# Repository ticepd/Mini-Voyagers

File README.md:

# Mini-Voyager-1 & Mini-Voyager-2 schematic and board files

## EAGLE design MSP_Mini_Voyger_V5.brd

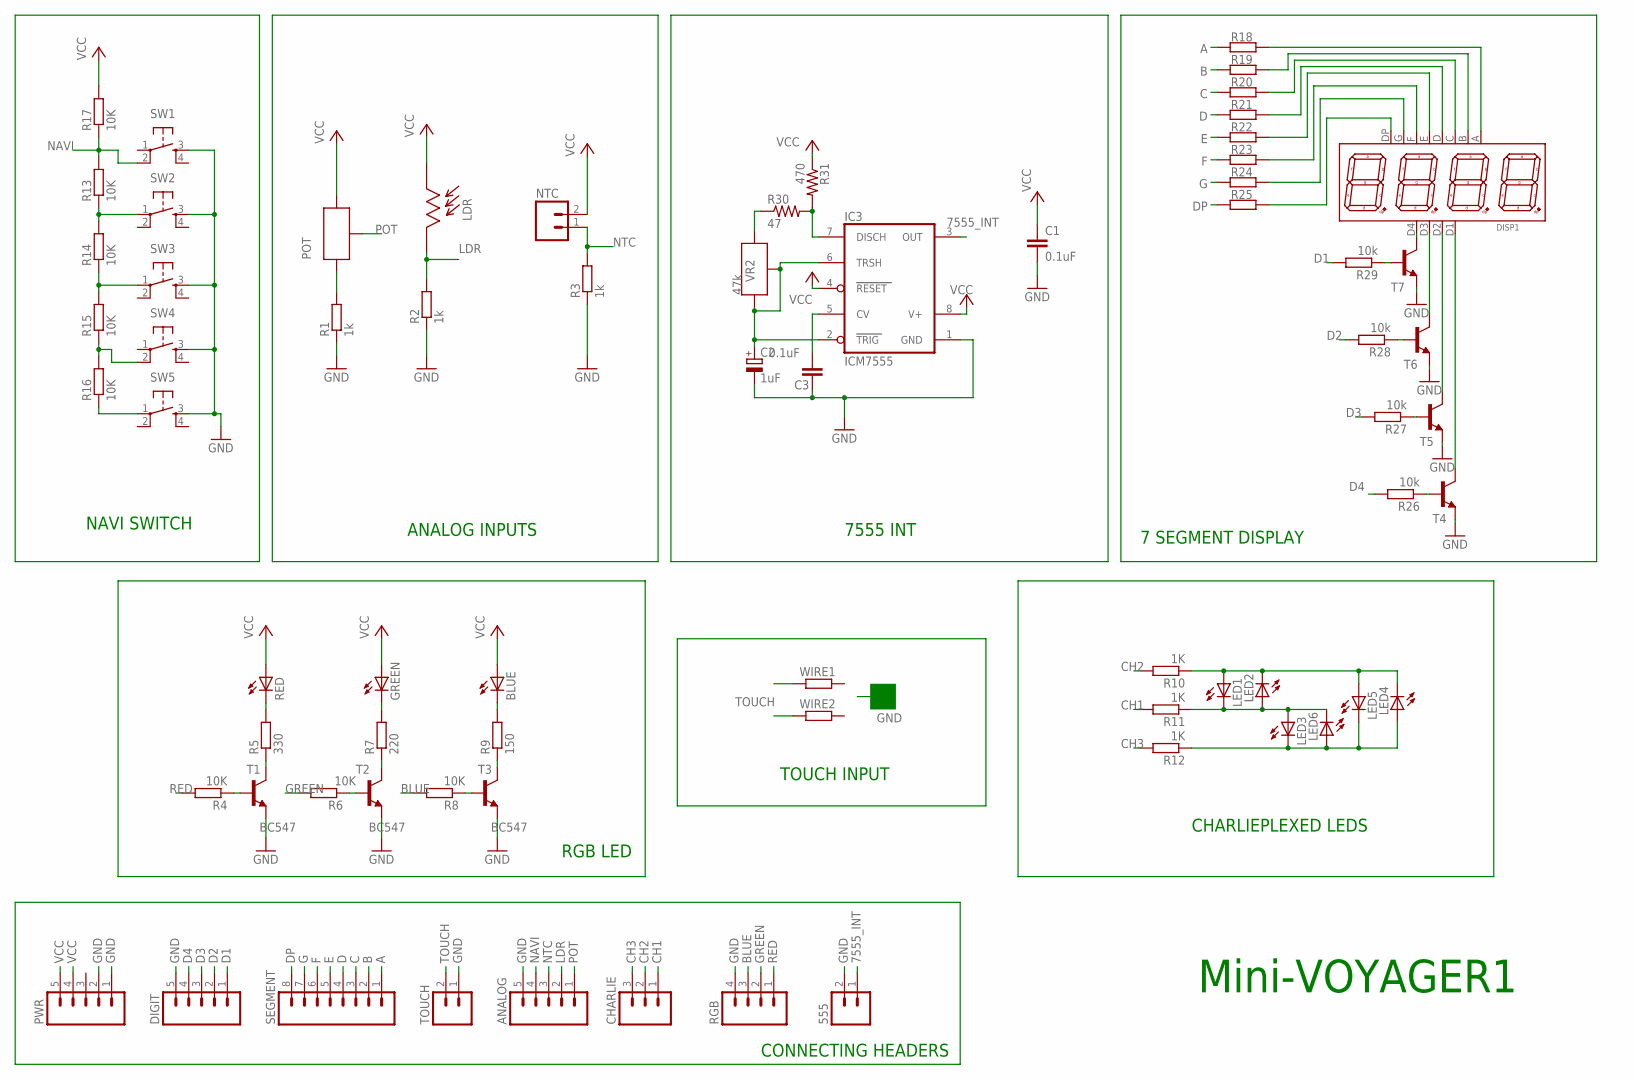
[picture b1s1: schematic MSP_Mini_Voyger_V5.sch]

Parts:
555: M02; 02P
ANALOG: M05; 05P
BLUE: LED5MM
C1: 0.1uF; C050-024X044
C2: 1uF; E2,5-7
C3: 0.1uF; C025-024X044
CHARLIE: M03; 03P
DIGIT: M05; 05P
DISP1: 7-SEG_4D_0.36; 7SEG-4DIG
GREEN: LED5MM
IC3: ICM7555; DIL08
LDR: CDSLDR3MM; LDR3MM
LED1, LED2, LED3, LED4, LED5, LED6: LED3MM
NTC: M02; 02P
POT: POTNORMAL; RJ9W
PWR: M05; 05P
R1, R2, R3: 1k; 0207/10
R4, R6, R8: 10K; 0207/7
R5: 330; 0207/7
R7: 220; 0207/7
R9: 150; 0207/7
R10, R11, R12: 1K; 0207/10
R13, R14, R15, R16, R17: 10K; 0207/10
R18, R19, R20, R21, R22, R23, R24, R25: 1k; 0207/7
R26, R27, R28, R29: 10k; 0207/7
R30: 47; 0207/7
R31: 470; 0207/7
RED: LED5MM
RGB: M04; 04P
SEGMENT: M08; 08P
SW1, SW2, SW3, SW4, SW5: OMRON_SWITCH_10-XX; B3F-10XX
T1, T2, T3, T4, T5, T6, T7: BC547; TO92
TOUCH: M02; 02P
VR2: 47k; RJ9W
WIRE1, WIRE2: R-EU_0207/15; 0207/15

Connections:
7555_INT: 555.1, IC3.3 (OUT)
A: R18.2, SEGMENT.1
B: R19.2, SEGMENT.2
BLUE: R8.2, RGB.3
C: R20.2, SEGMENT.3
CH1: CHARLIE.1, R11.2
CH2: CHARLIE.2, R10.2
CH3: CHARLIE.3, R12.2
D: R21.2, SEGMENT.4
D1: DIGIT.1, R29.2
D2: DIGIT.2, R28.2
D3: DIGIT.3, R27.2
D4: DIGIT.4, R26.2
DP: R25.2, SEGMENT.8
E: R22.2, SEGMENT.5
F: R23.2, SEGMENT.6
G: R24.2, SEGMENT.7
GND: 555.2, ANALOG.5, C1.2, C2.-, C3.2, DIGIT.5, IC3.1 (GND), PWR.1, PWR.2, R1.1, R2.1, R3.1, RGB.4, SW1.3 (S), SW2.3 (S), SW3.3 (S), SW4.3 (S), SW5.3 (S), T1.1 (E), T2.1 (E), T3.1 (E), T4.1 (E), T5.1 (E), T6.1 (E), T7.1 (E), TOUCH.1
GREEN: R6.2, RGB.2
LDR: ANALOG.2, LDR.P$2, R2.2
unnamed: POT.E, R1.2
unnamed: LED1.A, LED2.K (C), LED4.K (C), LED5.A, R10.1
unnamed: IC3.7 (DISCH), R30.2, R31.2
unnamed: R5.1, T1.3 (C)
unnamed: DISP1.D1, T4.3 (C)
unnamed: DISP1.D4, T7.3 (C)
unnamed: DISP1.A, R18.1
unnamed: DISP1.B, R19.1
unnamed: R4.1, T1.2 (B)
unnamed: R13.1, R14.2, SW2.1
unnamed: R14.1, R15.2, SW3.1
unnamed: R15.1, R16.2, SW4.2 (P1)
unnamed: R16.1, SW5.1
unnamed: R6.1, T2.2 (B)
unnamed: DISP1.C, R20.1
unnamed: DISP1.D, R21.1
unnamed: R5.2, RED.K (C)
unnamed: GREEN.K (C), R7.2
unnamed: DISP1.E, R22.1
unnamed: R8.1, T3.2 (B)
unnamed: R9.1, T3.3 (C)
unnamed: BLUE.K (C), R9.2
unnamed: R26.1, T4.2 (B)
unnamed: R27.1, T5.2 (B)
unnamed: R28.1, T6.2 (B)
unnamed: R29.1, T7.2 (B)
unnamed: DISP1.D2, T5.3 (C)
unnamed: DISP1.D3, T6.3 (C)
unnamed: DISP1.F, R23.1
unnamed: DISP1.G, R24.1
unnamed: DISP1.DP, R25.1
unnamed: C2.+, IC3.2 (TRIG), IC3.6 (TRSH), VR2.E, VR2.S
unnamed: R30.1, VR2.A
unnamed: C3.1, IC3.5 (CV)
unnamed: LED3.K (C), LED4.A, LED5.K (C), LED6.A, R12.1
unnamed: LED1.K (C), LED2.A, LED3.A, LED6.K (C), R11.1
NAVI: ANALOG.4, R13.2, R17.1, SW1.2 (P1)
NTC: ANALOG.3, NTC.1, R3.2
POT: ANALOG.1, POT.S
R7: R7.1, T2.3 (C)
RED: R4.2, RGB.1
TOUCH: TOUCH.2, WIRE1.1, WIRE2.1
VCC: BLUE.A, C1.1, GREEN.A, IC3.4 (RESET), IC3.8 (V+), LDR.P$1, NTC.2, POT.A, PWR.4, PWR.5, R17.2, R31.1, RED.A

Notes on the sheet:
NAVI SWITCH
ANALOG INPUTS
RGB LED
7 SEGMENT DISPLAY
TOUCH INPUT
CHARLIEPLEXED LEDS
7555 INT
CONNECTING HEADERS
Mini-VOYAGER1

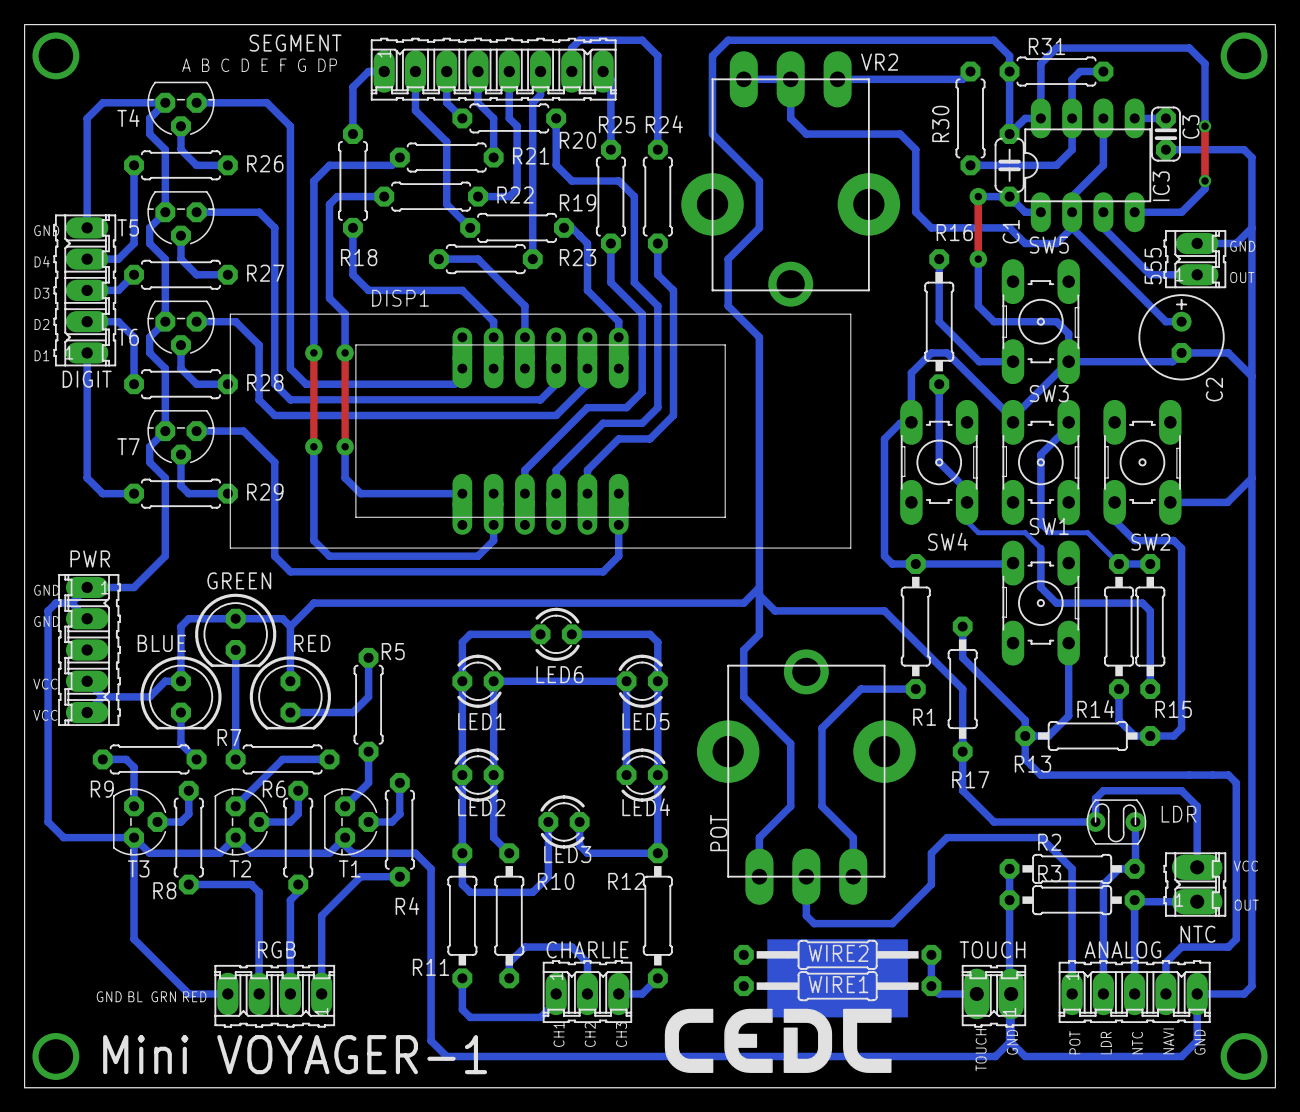
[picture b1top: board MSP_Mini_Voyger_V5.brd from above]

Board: 2 copper layers, 101.6 x 86.4 mm, 72 parts (0 on the bottom side), 63 nets.

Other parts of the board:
U$1: LOGO-CEDT-SILK-18MM

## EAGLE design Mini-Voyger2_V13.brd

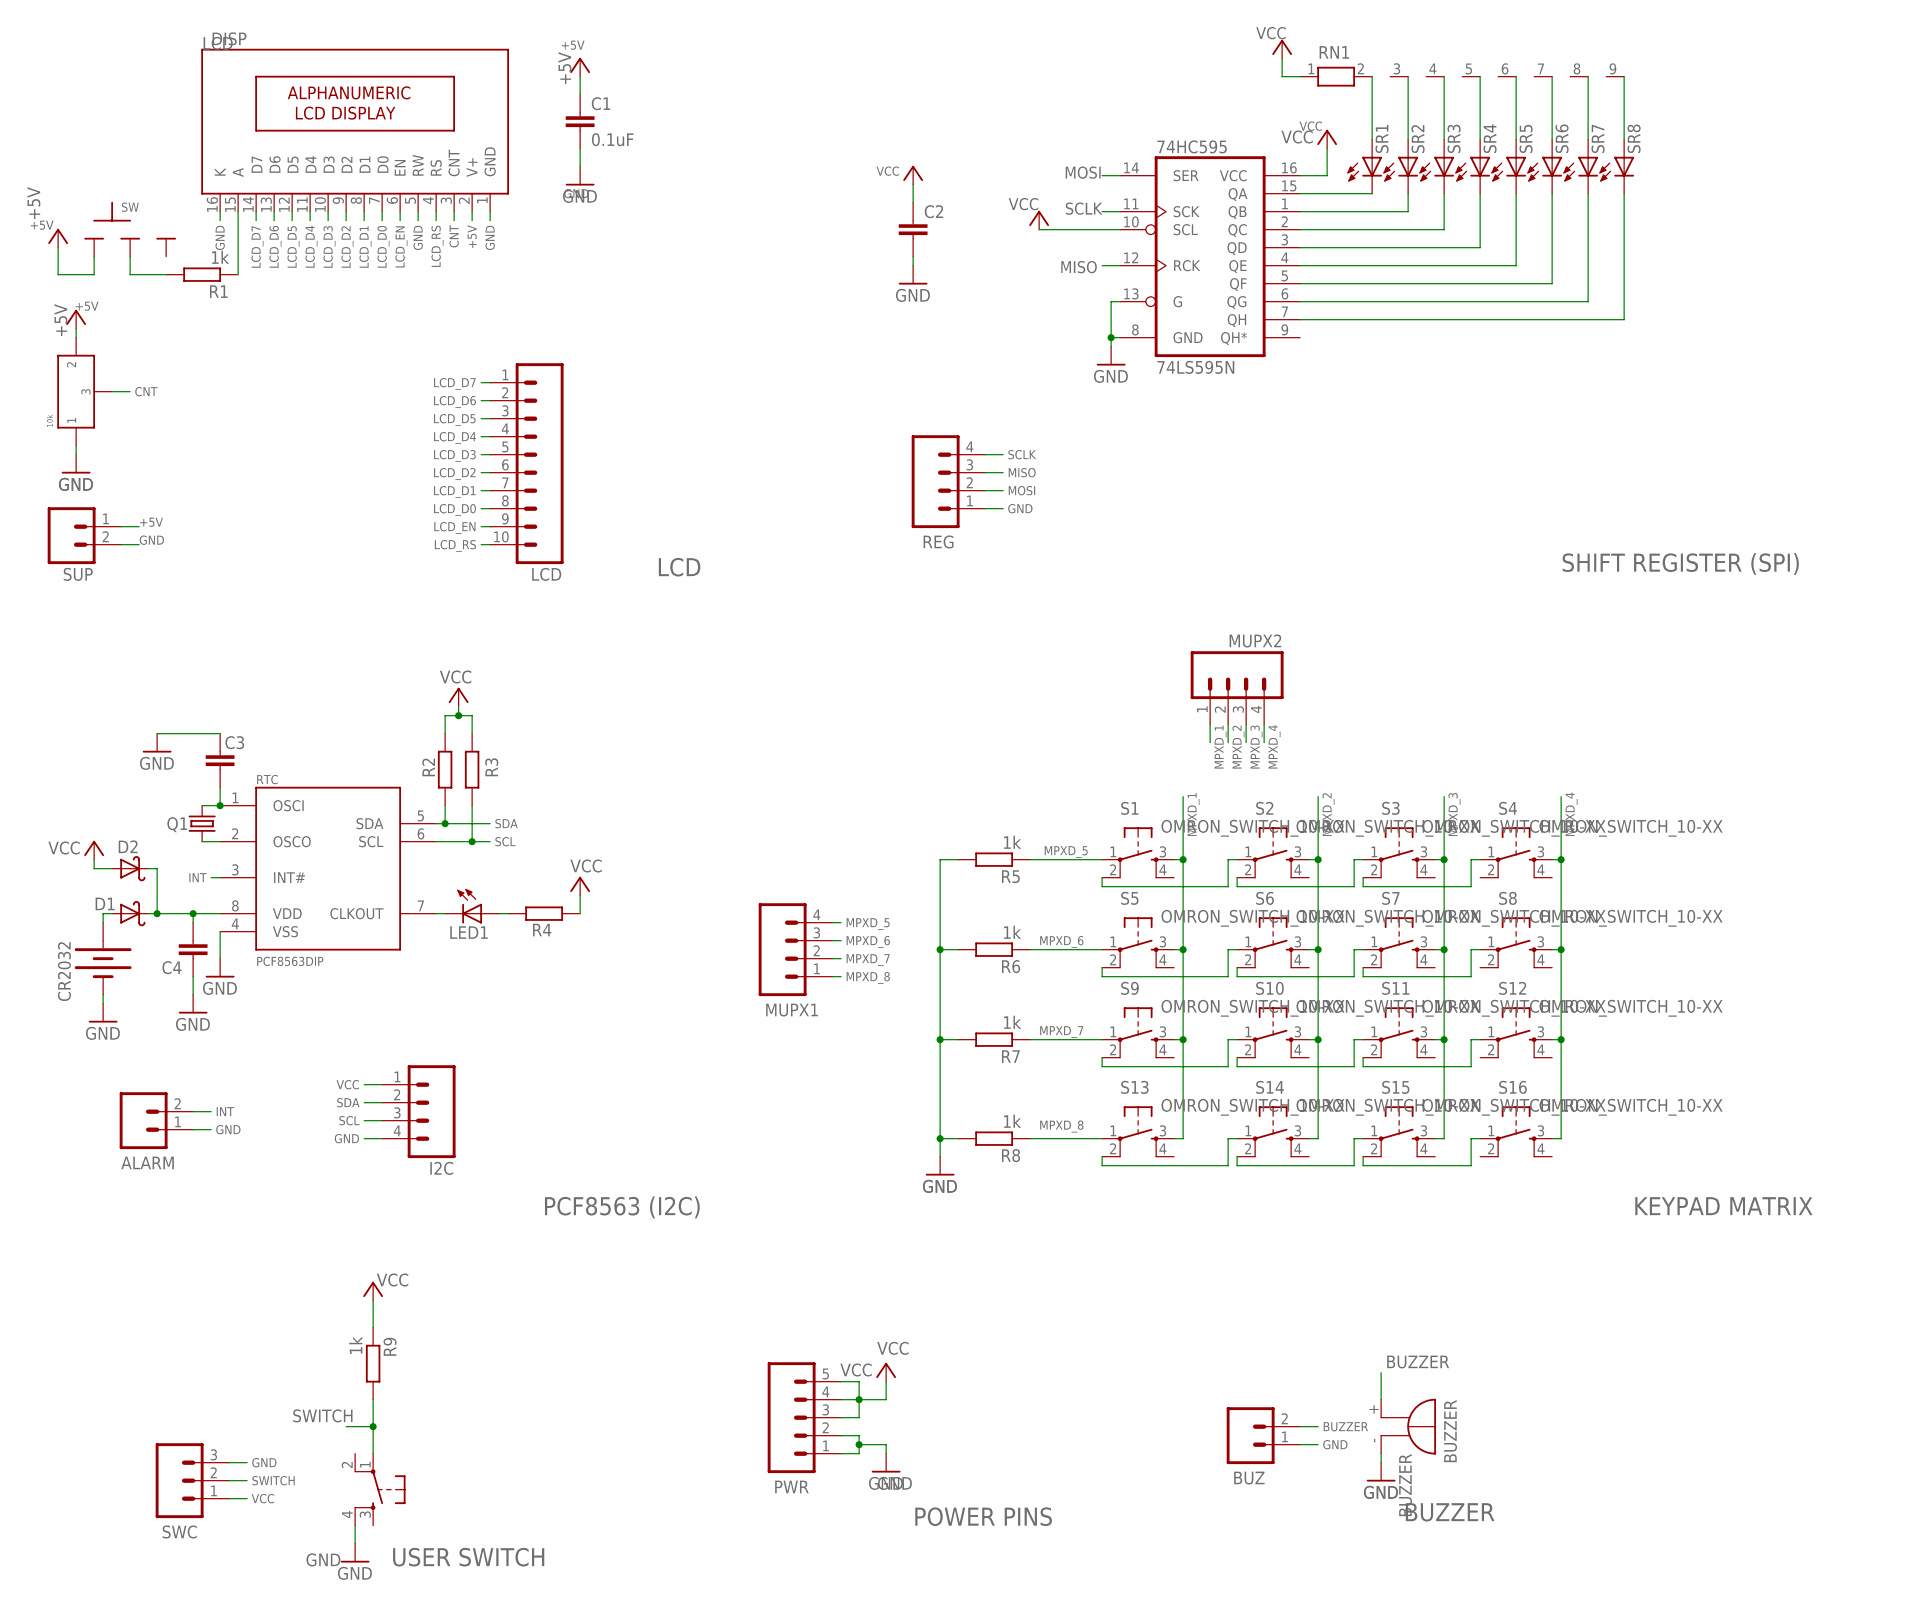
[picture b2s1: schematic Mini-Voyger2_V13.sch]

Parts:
74HC595: 74LS595N; DIL16
ALARM: M02; 02P
BUZ: M02; 02P
BUZZER: BUZZER; F/TMB
C1: 0.1uF; C025-024X044
C2: 0.1uF; C025-025X050
C3: 22pF; C025-024X044
C4: 0.1uF; C050-025X075
CR2032: BATTERY20PTH; BATTCOM_20MM_PTH
D1, D2: 1N5819; DO41-10
DISP: LCD; 16X2_LCD
I2C: M04; 04P
LCD: M10; 10P
LED1: LED3MM
MUPX1, MUPX2: M04; 04P
PRESET: 10k; PRESET_LR
PWR: M05; 05P
Q1: 32678Hz; TC26H
R1, R5, R6, R7, R8, R9: 1k; 0207/7
R2, R3: 10k; 0207/7
R4: 470; 0207/7
REG: M04; 04P
RN1: 1k; RN-9
RTC: PCF8563DIP; DIL08
S1, S2, S3, S4, S5, S6, S7, S8, S9, S10, S11, S12, S13, S14, S15, S16: OMRON_SWITCH_10-XX; B3F-10XX
SR1, SR2, SR3, SR4, SR5, SR6, SR7, SR8: LED3MM
SUP: M02; 02P
SW: SLIDESWITCH-BIG; BIGSWITCH
SW1: OMRON_SWITCH_10-XX; B3F-10XX
SWC: M03; 03P

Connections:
+5V: C1.1, DISP.2 (V+), PRESET.P$2 (2), SUP.1, SW.1
BUZZER: BUZ.2, BUZZER.+
CNT: DISP.3 (CNT), PRESET.P$3 (3)
GND: 74HC595.8 (GND), 74HC595.13 (G), ALARM.1, BUZ.1, BUZZER.-, C1.2, C2.2, C3.2, C4.1, CR2032.2 (-), DISP.1 (GND), DISP.5 (RW), DISP.16 (K), I2C.4, PRESET.P$1 (1), PWR.1, PWR.2, R5.2, R6.2, R7.2, R8.2, REG.1, RTC.4 (VSS), SUP.2, SW1.4 (S1), SWC.3
INT: ALARM.2, RTC.3 (INT#)
LCD_D0: DISP.7 (D0), LCD.8
LCD_D1: DISP.8 (D1), LCD.7
LCD_D2: DISP.9 (D2), LCD.6
LCD_D3: DISP.10 (D3), LCD.5
LCD_D4: DISP.11 (D4), LCD.4
LCD_D5: DISP.12 (D5), LCD.3
LCD_D6: DISP.13 (D6), LCD.2
LCD_D7: DISP.14 (D7), LCD.1
LCD_EN: DISP.6 (EN), LCD.9
LCD_RS: DISP.4 (RS), LCD.10
MISO: 74HC595.12 (RCK), REG.3
MOSI: 74HC595.14 (SER), REG.2
MPXD_1: MUPX2.1, S1.3 (S), S5.3 (S), S9.3 (S), S13.3 (S)
MPXD_2: MUPX2.2, S2.3 (S), S6.3 (S), S10.3 (S), S14.3 (S)
MPXD_3: MUPX2.3, S3.3 (S), S7.3 (S), S11.3 (S), S15.3 (S)
MPXD_4: MUPX2.4, S4.3 (S), S8.3 (S), S12.3 (S), S16.3 (S)
MPXD_5: MUPX1.4, R5.1, S1.1
MPXD_6: MUPX1.3, R6.1, S5.1
MPXD_7: MUPX1.2, R7.1, S9.1
MPXD_8: MUPX1.1, R8.1, S13.1
unnamed: C4.2, D1.C, D2.C, RTC.8 (VDD)
unnamed: R1.2, SW.2
unnamed: 74HC595.15 (QA), SR1.K (C)
unnamed: 74HC595.2 (QC), SR3.K (C)
unnamed: S1.2 (P1), S2.1
unnamed: S2.2 (P1), S3.1
unnamed: S3.2 (P1), S4.1
unnamed: S5.2 (P1), S6.1
unnamed: S6.2 (P1), S7.1
unnamed: S7.2 (P1), S8.1
unnamed: S9.2 (P1), S10.1
unnamed: S10.2 (P1), S11.1
unnamed: S11.2 (P1), S12.1
unnamed: S13.2 (P1), S14.1
unnamed: S14.2 (P1), S15.1
unnamed: S15.2 (P1), S16.1
unnamed: 74HC595.3 (QD), SR4.K (C)
unnamed: DISP.15 (A), R1.1
unnamed: 74HC595.4 (QE), SR5.K (C)
unnamed: 74HC595.5 (QF), SR6.K (C)
unnamed: 74HC595.6 (QG), SR7.K (C)
unnamed: 74HC595.7 (QH), SR8.K (C)
unnamed: 74HC595.1 (QB), SR2.K (C)
unnamed: RN1.2, SR1.A
unnamed: RN1.3, SR2.A
unnamed: RN1.4, SR3.A
unnamed: RN1.5, SR4.A
unnamed: RN1.6, SR5.A
unnamed: RN1.7, SR6.A
unnamed: RN1.8, SR7.A
unnamed: RN1.9, SR8.A
unnamed: CR2032.1 (+), D1.A
unnamed: Q1.1, RTC.2 (OSCO)
unnamed: C3.1, Q1.2, RTC.1 (OSCI)
unnamed: LED1.A, R4.1
unnamed: LED1.K (C), RTC.7 (CLKOUT)
SCL: I2C.3, R3.2, RTC.6 (SCL)
SCLK: 74HC595.11 (SCK), REG.4
SDA: I2C.2, R2.2, RTC.5 (SDA)
SWITCH: R9.2, SW1.1, SWC.2
VCC: 74HC595.10 (SCL), 74HC595.16 (VCC), C2.1, D2.A, I2C.1, PWR.3, PWR.4, PWR.5, R2.1, R3.1, R4.2, R9.1, RN1.1, SWC.1

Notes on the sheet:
SHIFT REGISTER (SPI)
PCF8563 (I2C)
POWER PINS
BUZZER
USER SWITCH
LCD
KEYPAD MATRIX

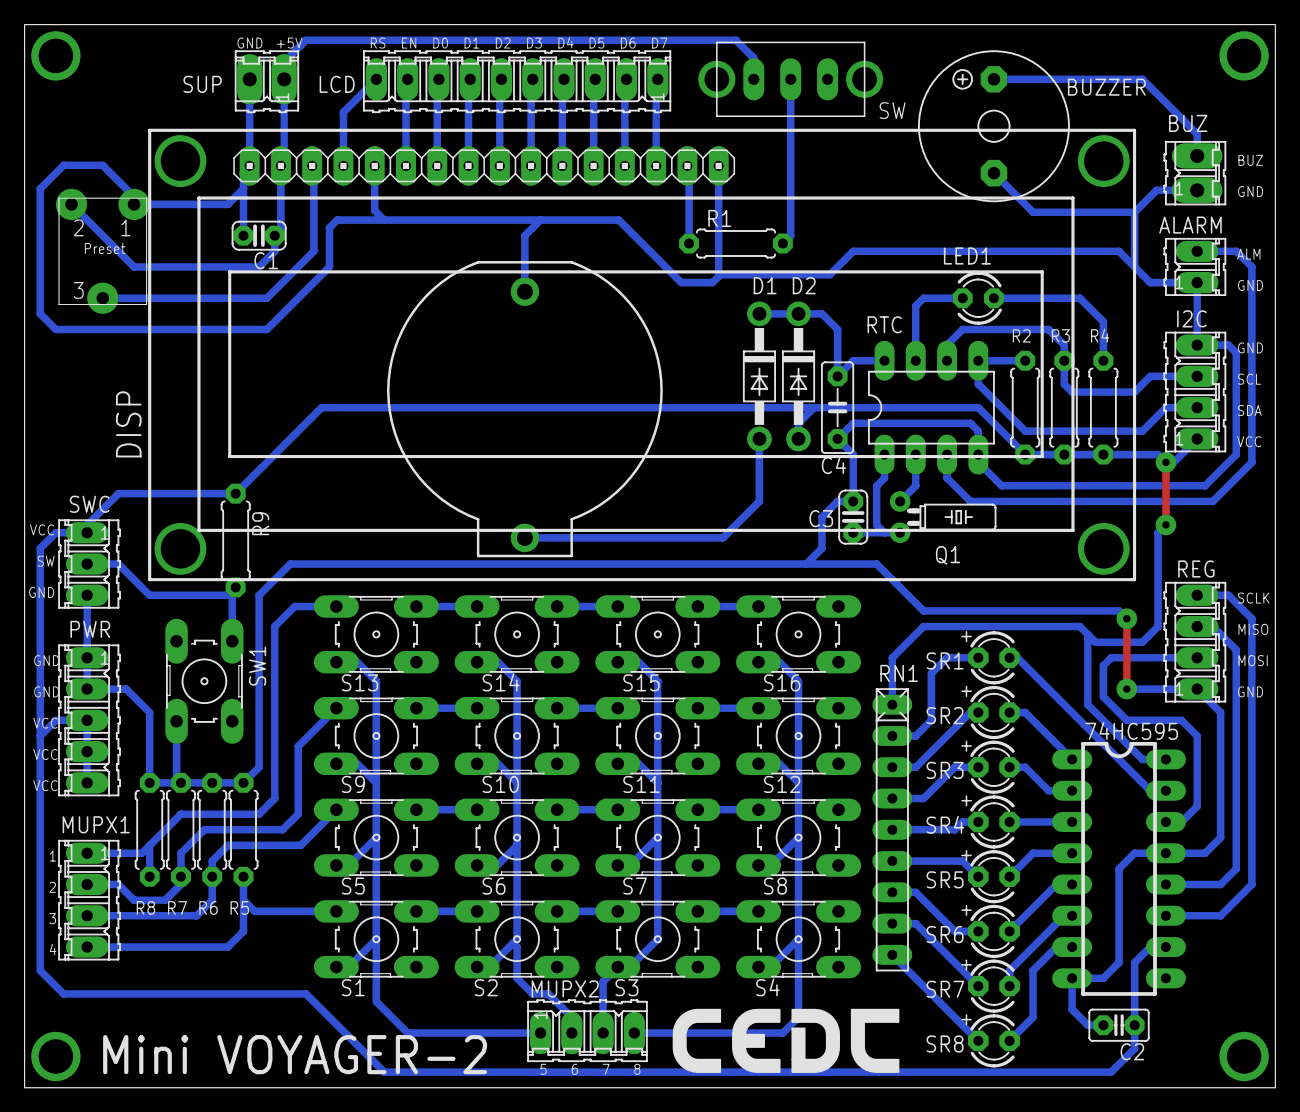
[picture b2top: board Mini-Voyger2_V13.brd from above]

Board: 2 copper layers, 101.6 x 86.4 mm, 61 parts (0 on the bottom side), 66 nets.

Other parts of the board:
U$2: LOGO-CEDT-SILK-18MM

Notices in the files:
parts and their libraries:
SparkFun-DigitalIC: Licensing: Creative Commons ShareAlike 4.0 International - https://creativecommons.org/licenses/by-sa/4.0
